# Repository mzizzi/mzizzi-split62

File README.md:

# split62

My take on a low profile split keyboard. 

* [x] Low profile choc 1350 switches
* [x] Hot swappable
* [x] Split layout
* [x] Ortholinear
* [x] Column staggered

This was a really rewarding project and I learned a bunch along the way! I hope that this 
repo and documentation help you build your own. That said...

**Disclaimer:** While the keyboard is working while I type out this readme, there may be 
errors and/or poorly designed componetents throughout this repository. Use these files 
at your own risk. Please also read through the [TODO](#TODO) section before deciding to 
use anything in this repository.

## Firmware

This keyboard's firmware is built using QMK.

[Set up QMK](https://docs.qmk.fm/newbs_getting_started) locally and copy `qmk/keyboards/mzizzi`
 from this repository into your local qmk keyboards directory.

Connect one half of the keyboard and put the elite-pi into bootloader mode. keeb.io has excellent 
documentation on flashing firmware to the elite-pi: https://docs.keeb.io/elite-pi-guide#flashing

Enter bootloader mode (use one of the following methods):
* For a new Elite-Pi out of the packaging, it will already start in bootloader mode when plugged 
  into the computer
* Hold the Boot button (the left button) down, while pluging in the USB-C cable
* Wait for OS to detect the Elite-Pi. It will show up as a USB mass-storage device named RPI-RP2.

After the initial flash of the board you can simply hold down top innermost key (5 or 6 depending 
on the hand) while plugging in the elite-pi to make it connect in bootloader mode.

Each half of the keyboard must be flashed separately with qmk 
[handedness](https://docs.qmk.fm/features/split_keyboard#handedness-by-eeprom) flags specifying 
which side is being flashed. Both halves must be flashed:

```
qmk flash -kb mzizzi/split62 -km via -bl uf2-split-left
or
qmk flash -kb mzizzi/split62 -km via -bl uf2-split-right
```

## Configuration with via

This keyboard's firmware is compiled with support for [VIA](https://www.caniusevia.com/) which 
will allow for the keymap to be modified on the fly. The 
[via documentation](https://www.caniusevia.com/docs/specification) covers everything needed to 
get via working with the split62.

* Flash the keyboard via the instructions in this readme.
* Open https://usevia.app/ in your web browser
* Enable design mode in via settings
* Upload `qmk/keyboards/mzizzi/split62/via.json` in the design tab
* Authorize via access to the device
* Start customizing!                                                                                  |

## PCB

The PCB for this board was designed with [ergogen](https://ergogen.xyz/). I highly recommend
reading the [flatfootfox ergogen introducution](https://flatfootfox.com/ergogen-introduction/)
if you're looking to modify this board or make your own.

The PCB for this keyboard is reversible to cut down on cost of having it manufactured. Most board
manufacturers have a minimum order quantity per design (5 boards for jlcpcb). This makes for an 
interesting footprint for the elite-pi. The board is marked on either side to try and make it 
harder to accidentally install the controller socket on the wrong side.

All of the gerber files that I used to order these boards are included in the `gerbers` directory. 
Please read the [TODO](#TODO) section below before deciding whether or not to use these 
files as-is.

## Case

The case for the split62 is 3d printed. The outter shell of the case also serves as a key-plate to 
lock the choc switches into position. Ergogen is not used to generate the stls for the case.
Instead ergogen is used to generate dxfs for a "keyplate" outline. I imported that outline into
another CAD program and used it as a starting point to model the case. I printed the case on a 
bambulab x1c with 0.2mm layer height using 
[Overture matte black PLA](https://www.amazon.com/gp/product/B089S2QDHD)

## Bill of Materials

I built this keyboard for around $200 but also have a bunch of spare parts left over. 
[keeb.io](https://keeb.io/) links because they're awesome and did same day order+pickup for 
components that weren't even listed on their site!

| Item                      | Count | Cost    | Notes                                                                                                                                                                                      |
| ------------------------- | ----- | ------- | ------------------------------------------------------------------------------------------------------------------------------------------------------------------------------------------ |
| 5x PCB                    | 5     | $21.00  | Only 2x needed. 5x minimum order from JLCPCB                                                                                                                                               |
| 3D Printed Cases          | 1     | $5.00   | Probably less if you have a printer (or know someone with a printer!)                                                                                                                      |
| Elite-Pi Controllers      | 2     | $26.00  | [https://keeb.io/products/elite-pi-usb-c-pro-micro-replacement-rp2040](https://keeb.io/products/elite-pi-usb-c-pro-micro-replacement-rp2040)                                               |
| Controller sockets        | 2     | $10.00  | Not required but recommended: [https://www.amazon.com/gp/product/B07H3SK179](https://www.amazon.com/gp/product/B07H3SK179)                                                                 |
| Kailh 1350 switches       | 62    | $38.00  | [https://keeb.io/products/kailh-choc-low-profile-switches-v1](https://keeb.io/products/kailh-choc-low-profile-switches-v1)                                                                 |
| Kailh 1350 sockets        | 62    | $16.00  | [https://www.amazon.com/100Pieces-Chocolate-Switches-Accessories-Mechanical-PC/dp/B0CPVJLMDJ](https://www.amazon.com/100Pieces-Chocolate-Switches-Accessories-Mechanical-PC/dp/B0CPVJLMDJ) |
| 1N4148 SMT SOD-123 Diodes | 62    | $10.00  | [https://www.amazon.com/gp/product/B09DR5KFXM](https://www.amazon.com/gp/product/B09DR5KFXM)                                                                                               |
| PJ-320A TRRS jacks        | 2     | $1.00   | [https://keeb.io/products/trrs-jack-3-5mm](https://keeb.io/products/trrs-jack-3-5mm)                                                                                                       |
| Choc 1350 Keycaps         | 62    | $54.00  | [https://keeb.io/products/mbk-glow-r2-choc-keycap-set](https://keeb.io/products/mbk-glow-r2-choc-keycap-set)                                                                               |
| TRRS Cable                | 1     | $4.00   | [https://keeb.io/products/trrs-cable?variant=50550149190](https://keeb.io/products/trrs-cable?variant=50550149190)                                                                         |
| m2 screws                 | 8     | $7.00   | [https://www.amazon.com/Countersunk-DIN7991-Stainless-Threaded-Fasteners/dp/B0CG1PDBWN](https://www.amazon.com/Countersunk-DIN7991-Stainless-Threaded-Fasteners/dp/B0CG1PDBWN)             |
| m2 threaded inserts       | 8     | $8.00   | [https://www.amazon.com/gp/product/B0B8GN63S2](https://www.amazon.com/gp/product/B0B8GN63S2)                                                                                               |
| Rubber feet               | 8     | $3.00   | [https://keeb.io/products/skuf-silicone-rubber-keyboard-feet](https://keeb.io/products/skuf-silicone-rubber-keyboard-feet)                                                                 |
| Total                     |       | $203    |                                                                                                          

## TODO

* Put the trrs jack closer to the side of the board. I had to cut away a few millimeters of the 
  board with a rotary tool so that the trrs connector had clearance to be fully inserted.
* Double check the trace size for 3v3 power and ground over the trrs cable. I used whatever the 
  default was without looking into how much power the rp2040 consumes. Google says that the rp2040 
  draws 20mA peak.
* More mounting holes on the PCB. A few more wouldn't hurt and would help with any warping of the
  3d printed case.
* Pull the sides of the PCB in a few mm. I didn't account for the case adding another 1-2mm.
* A better way to attach the MCU cover. This was an afterthought in v1 and attached with 
  double sided foam tape.
* Optional tenting mounts for the base of the case.
* Aluminum case

## Helpful Resources

Links to pages that helped me along the way:

* An excellent guide on using ergogen: https://flatfootfox.com/ergogen-introduction/
* qmk's documentation on a keyboard matrix and how it works:
  https://docs.qmk.fm/how_a_matrix_works
  * This article is what really made it stick for me: 
    https://www.dribin.org/dave/keyboard/one_html/
* The qmk hand wiring guide is a good introduction what you will later design a 
  pcb for: https://docs.qmk.fm/hand_wire 
* Matrix configuration: https://docs.qmk.fm/porting_your_keyboard_to_qmk#matrix-configuration
* Split keyboard layout marco: https://docs.qmk.fm/features/split_keyboard#layout-macro
* via: https://www.caniusevia.com/docs/specification

## More pictures

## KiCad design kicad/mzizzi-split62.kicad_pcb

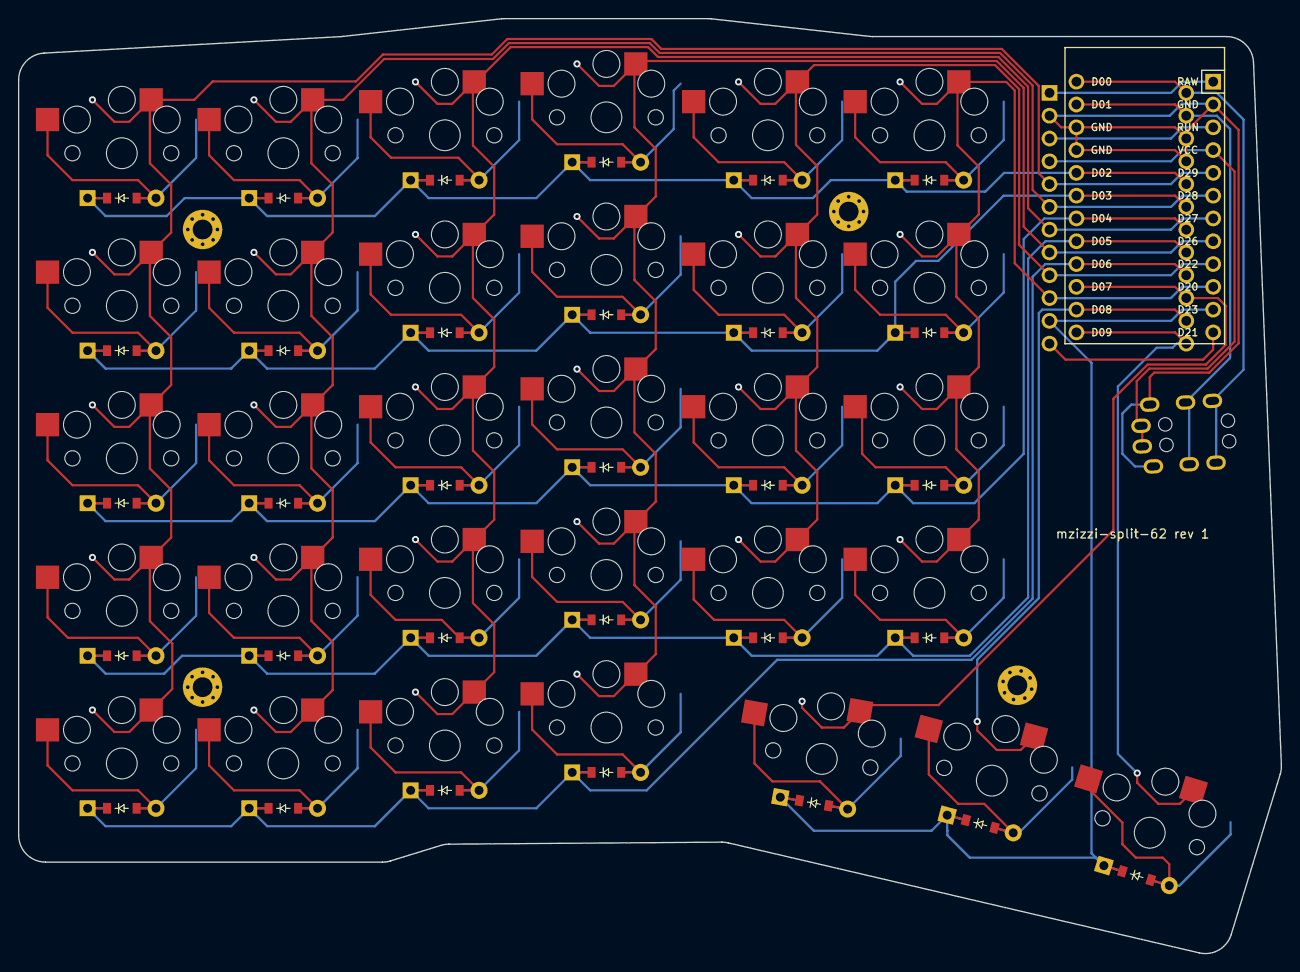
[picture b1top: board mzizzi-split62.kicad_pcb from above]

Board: 2 copper layers, 140.7 x 104.2 mm, 69 parts (0 on the bottom side), 53 nets.

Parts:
D1, D2, D3, D4, D5, D6, D7, D8, D9, D10, D11, D12, D13, D14, D15, D16, D17, D18, D19, D20, D21, D22, D23, D24, D25, D26, D27, D28, D29, D30, D31: ComboDiode
MCU1, MCU2: ElitePi
S1, S2, S3, S4, S5, S6, S7, S8, S9, S10, S11, S12, S13, S14, S15, S16, S17, S18, S19, S20, S21, S22, S23, S24, S25, S26, S27, S28, S29, S30, S31: PG1350
TRRS1: TRRS-PJ-320A-dual
_1, _2, _3, _4: MountingHole_2.2mm_M2_Pad_Via

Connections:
D0: MCU1.13, MCU2.13, TRRS1.4
D1: MCU1.14, MCU2.14, TRRS1.3
D2: D5.1, D10.1, D15.1, D20.1, D24.1, D28.1, MCU1.17, MCU2.17
D3: D4.1, D9.1, D14.1, D19.1, D23.1, D27.1, MCU1.18, MCU2.18
D4: D3.1, D8.1, D13.1, D18.1, D22.1, D26.1, MCU1.19, MCU2.19
D5: D2.1, D7.1, D12.1, D17.1, D21.1, D25.1, MCU1.20, MCU2.20
D6: D1.1, D6.1, D11.1, D16.1, MCU1.21, MCU2.21
D7: MCU1.22, MCU2.22, S29.1
D8: MCU1.23, MCU2.23, S30.1
D9: MCU1.24, MCU2.24, S31.1
D20: MCU1.10, MCU2.10, S25.1, S26.1, S27.1, S28.1
D21: MCU1.12, MCU2.12
D22: MCU1.9, MCU2.9, S21.1, S22.1, S23.1, S24.1
D23: D29.1, D30.1, D31.1, MCU1.11, MCU2.11
D26: MCU1.8, MCU2.8, S16.1, S17.1, S18.1, S19.1, S20.1
D27: MCU1.7, MCU2.7, S11.1, S12.1, S13.1, S14.1, S15.1
D28: MCU1.6, MCU2.6, S6.1, S7.1, S8.1, S9.1, S10.1
D29: MCU1.5, MCU2.5, S1.1, S2.1, S3.1, S4.1, S5.1
GND: MCU1.2, MCU1.15, MCU1.16, MCU2.2, MCU2.15, MCU2.16, TRRS1.2
RAW: MCU1.1, MCU2.1
RUN: MCU1.3, MCU2.3
VCC: MCU1.4, MCU2.4, TRRS1.1
index_bottom: D21.2, S21.2
index_home: D22.2, S22.2
index_num: D24.2, S24.2
index_top: D23.2, S23.2
inner_bottom: D25.2, S25.2
inner_home: D26.2, S26.2
inner_num: D28.2, S28.2
inner_top: D27.2, S27.2
middle_bottom: D17.2, S17.2
middle_home: D18.2, S18.2
middle_mod: D16.2, S16.2
middle_num: D20.2, S20.2
middle_top: D19.2, S19.2
outer_bottom: D2.2, S2.2
outer_home: D3.2, S3.2
outer_mod: D1.2, S1.2
outer_num: D5.2, S5.2
outer_top: D4.2, S4.2
pinky_bottom: D7.2, S7.2
pinky_home: D8.2, S8.2
pinky_mod: D6.2, S6.2
pinky_num: D10.2, S10.2
pinky_top: D9.2, S9.2
ring_bottom: D12.2, S12.2
ring_home: D13.2, S13.2
ring_mod: D11.2, S11.2
ring_num: D15.2, S15.2
ring_top: D14.2, S14.2
thumbInner_thumb: D29.2, S29.2
thumbMiddle_thumb: D30.2, S30.2
thumbOuter_thumb: D31.2, S31.2
